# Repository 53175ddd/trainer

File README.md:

# trainer でできること

Arduino を使ったプログラミング学習用の教材です．段階を踏んで様々なことを学ぶことができるよう開発を進めています．

## 本リポジトリで管理されているもの

- 専用の開発ボード
  - `./boards/`
- 各種サンプルコード
  - `./samples/`
- 各種ドキュメント（Web ページとして公開）
  - `./docs/`
- 関連リンク

## ハードウェア

実習用に，秋月電子で購入できる RP2040 搭載のマイコンボード「AE-RP2040」を使用するハードウェア「trainer-pico」を用意しています．

基板イメージ：<https://kicanvas.org/?repo=https%3A%2F%2Fgithub.com%2F53175ddd%2Ftrainer%2Ftree%2Fmaster%2Fboards%2Ftrainer-pico>

// 基板が出来上がったら Booth の購入リンクを追加する

## ドキュメント

// ある程度開発が進んでから整備する  
// `./docs/` 以下に配置し GitHub Pages で公開の上，そのリンクをここに貼る

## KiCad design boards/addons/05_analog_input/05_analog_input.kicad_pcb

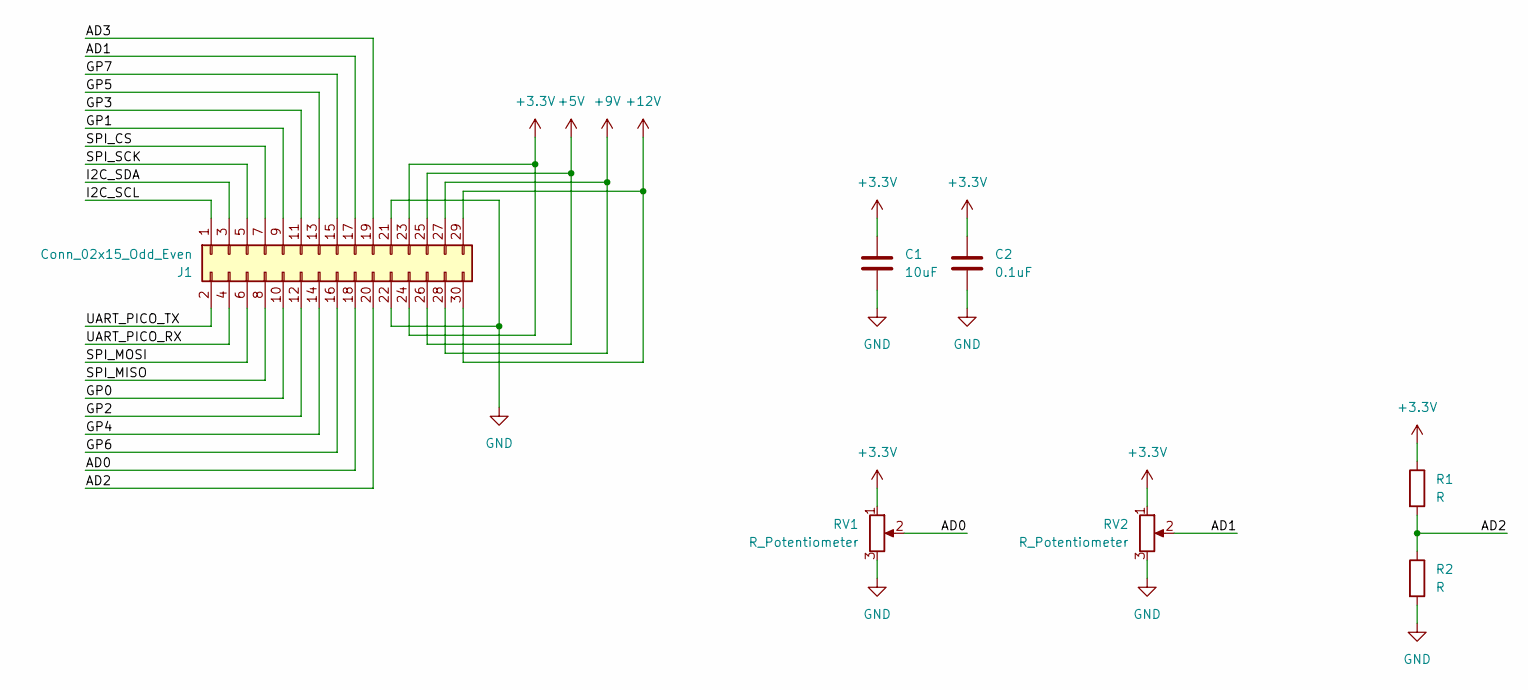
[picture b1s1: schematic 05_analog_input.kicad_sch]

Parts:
C1: 10uF; CP_Radial_D5.0mm_P2.00mm
C2: 0.1uF; C_Disc_D5.1mm_W3.2mm_P5.00mm
J1: Conn_02x15_Odd_Even; PinHeader_2x15_P2.54mm_Horizontal
R1: R; R_Radial_Power_L11.0mm_W7.0mm_P5.00mm
R2: R; R_Axial_DIN0207_L6.3mm_D2.5mm_P10.16mm_Horizontal
RV1, RV2: R_Potentiometer; Potentiometer_Bourns_PTA4543_Single_Slide

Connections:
+3.3V: C1.1, C2.1, J1.23, J1.24, R1.1, RV1.1, RV2.1
+5V: J1.25, J1.26
+9V: J1.27, J1.28
+12V: J1.29, J1.30
/AD0: J1.18, RV1.2
/AD1: J1.17, RV2.2
/AD2: J1.20, R1.2, R2.1
/AD3: J1.19
/GP0: J1.10
/GP1: J1.9
/GP2: J1.12
/GP3: J1.11
/GP4: J1.14
/GP5: J1.13
/GP6: J1.16
/GP7: J1.15
/I2C_SCL: J1.1
/I2C_SDA: J1.3
/SPI_CS: J1.7
/SPI_MISO: J1.8
/SPI_MOSI: J1.6
/SPI_SCK: J1.5
/UART_PICO_RX: J1.4
/UART_PICO_TX: J1.2
GND: C1.2, C2.2, J1.21, J1.22, R2.2, RV1.3, RV2.3

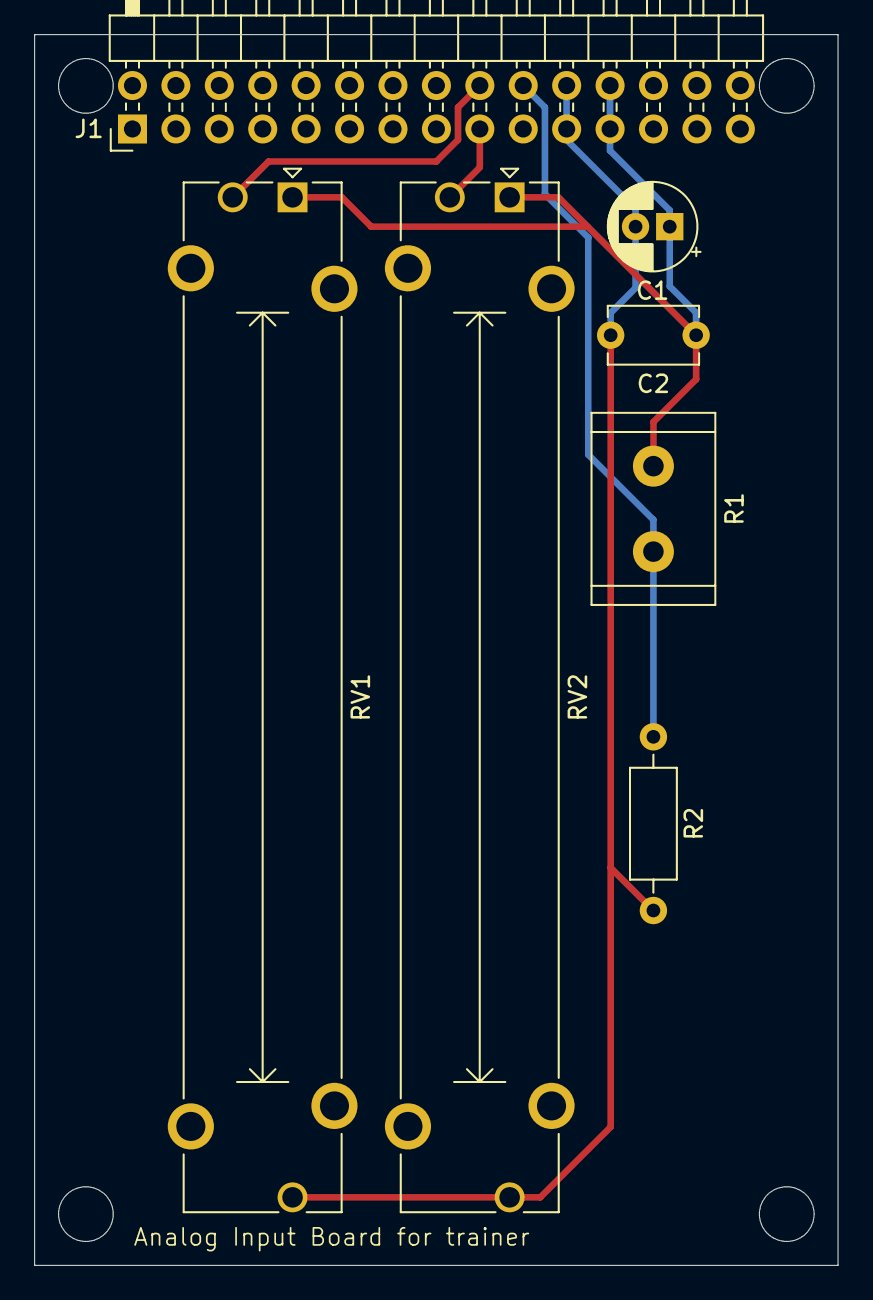
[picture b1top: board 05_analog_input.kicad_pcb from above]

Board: 2 copper layers, 47.0 x 72.0 mm, 7 parts (0 on the bottom side), 8 nets.

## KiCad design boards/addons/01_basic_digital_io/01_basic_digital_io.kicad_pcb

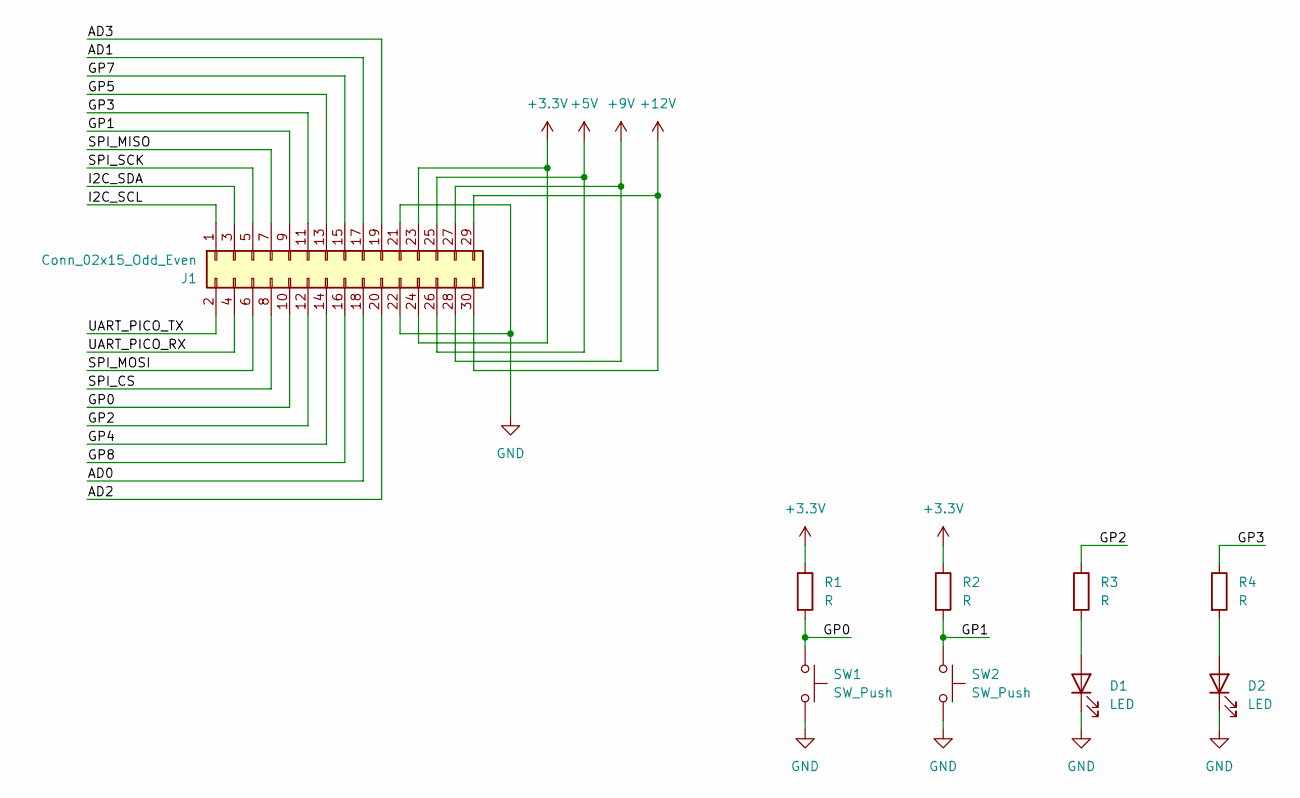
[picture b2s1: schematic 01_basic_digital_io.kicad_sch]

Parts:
D1, D2: LED; LED_D5.0mm
J1: Conn_02x15_Odd_Even; PinHeader_2x15_P2.54mm_Horizontal
R1, R2, R3, R4: R; R_Axial_DIN0207_L6.3mm_D2.5mm_P10.16mm_Horizontal
SW1, SW2: SW_Push; SW_PUSH-12mm

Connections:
+3.3V: J1.23, J1.24, R1.1, R2.1
+5V: J1.25, J1.26
+9V: J1.27, J1.28
+12V: J1.29, J1.30
/AD0: J1.18
/AD1: J1.17
/AD2: J1.20
/AD3: J1.19
/GP0: J1.10, R1.2, SW1.1
/GP1: J1.9, R2.2, SW2.1
/GP2: J1.12, R3.1
/GP3: J1.11, R4.1
/GP4: J1.14
/GP5: J1.13
/GP7: J1.15
/GP8: J1.16
/I2C_SCL: J1.1
/I2C_SDA: J1.3
/SPI_CS: J1.8
/SPI_SCK: J1.5
/UART_PICO_RX: J1.4
/UART_PICO_TX: J1.2
GND: D1.1 (K), D2.1 (K), J1.21, J1.22, SW1.2, SW2.2
unnamed: D1.2 (A), R3.2
unnamed: D2.2 (A), R4.2

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
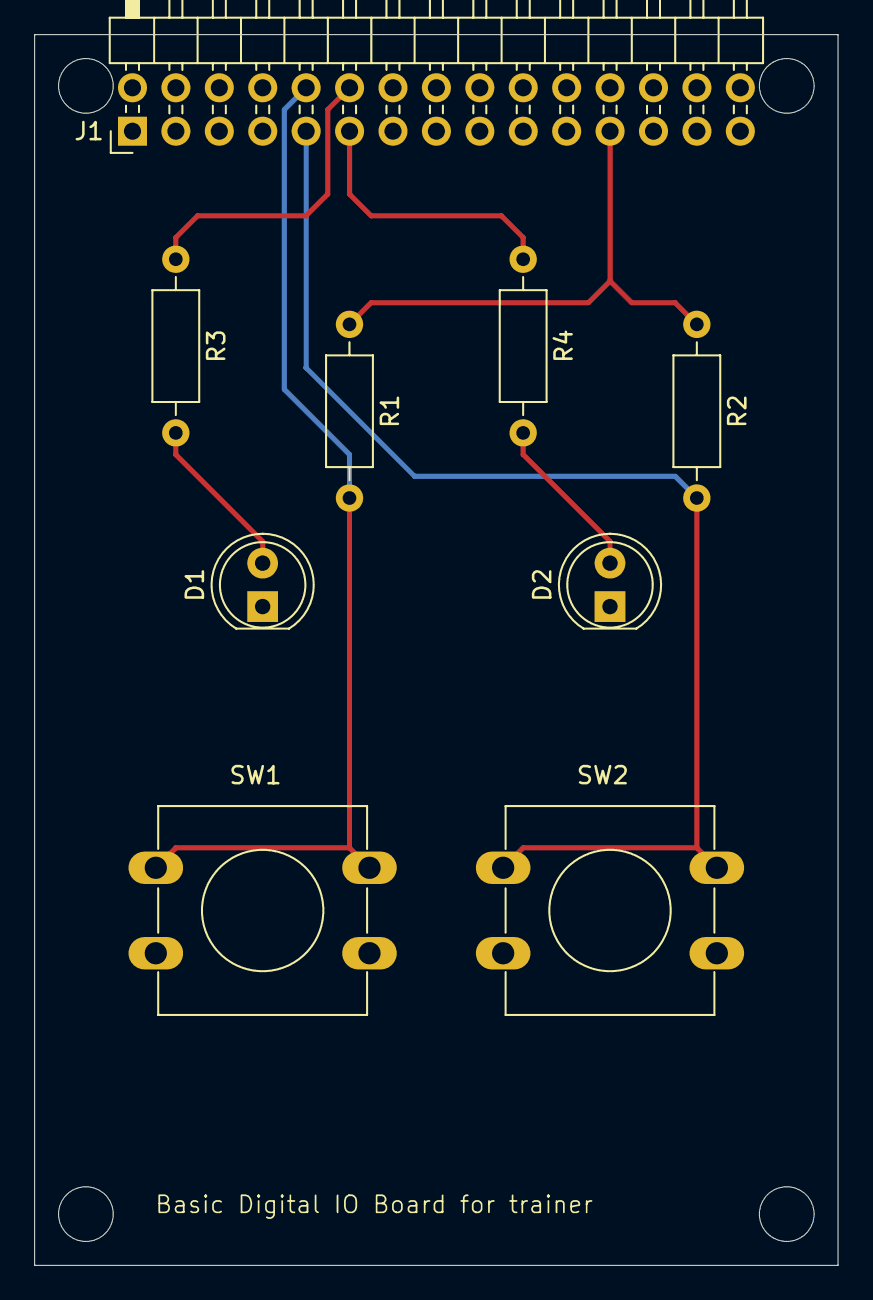
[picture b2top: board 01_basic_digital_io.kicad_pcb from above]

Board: 2 copper layers, 47.0 x 72.0 mm, 9 parts (0 on the bottom side), 12 nets.

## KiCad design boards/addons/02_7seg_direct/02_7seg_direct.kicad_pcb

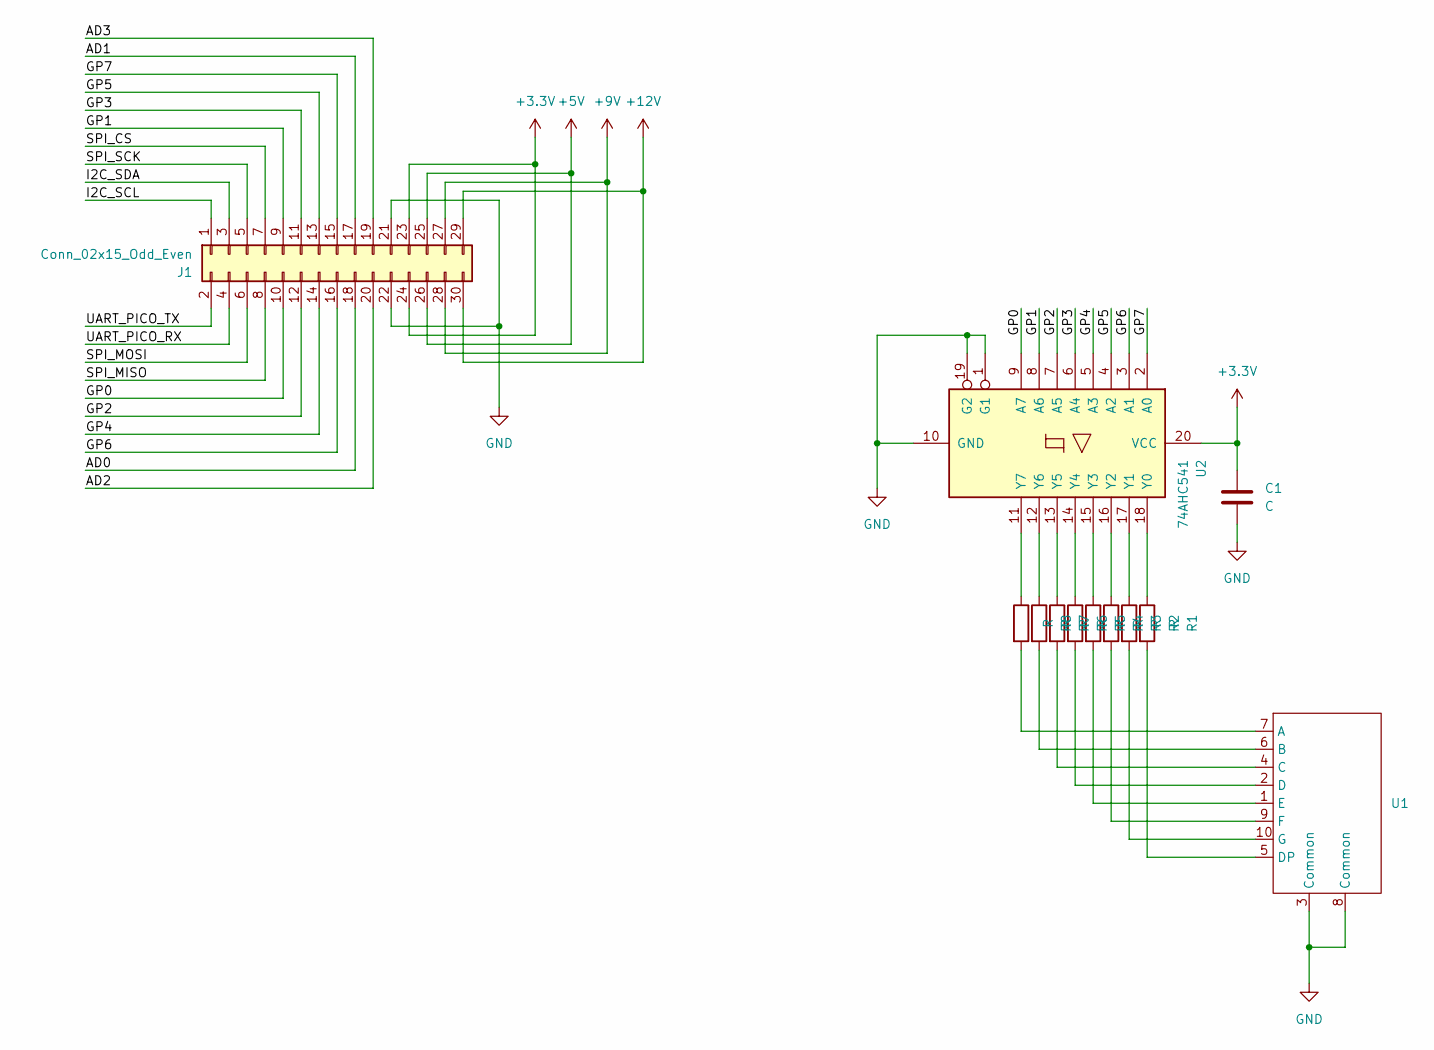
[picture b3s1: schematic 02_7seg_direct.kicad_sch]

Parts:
C1: C; C_Disc_D4.7mm_W2.5mm_P5.00mm
J1: Conn_02x15_Odd_Even; PinHeader_2x15_P2.54mm_Horizontal
R1, R2, R3, R4, R5, R6, R7, R8: R; R_Axial_DIN0207_L6.3mm_D2.5mm_P10.16mm_Horizontal
U1: OSL10561
U2: 74AHC541; DIP-20_W7.62mm_Socket

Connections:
+3.3V: C1.1, J1.23, J1.24, U2.20 (VCC)
+5V: J1.25, J1.26
+9V: J1.27, J1.28
+12V: J1.29, J1.30
/AD0: J1.18
/AD1: J1.17
/AD2: J1.20
/AD3: J1.19
/GP0: J1.10, U2.9 (A7)
/GP1: J1.9, U2.8 (A6)
/GP2: J1.12, U2.7 (A5)
/GP3: J1.11, U2.6 (A4)
/GP4: J1.14, U2.5 (A3)
/GP5: J1.13, U2.4 (A2)
/GP6: J1.16, U2.3 (A1)
/GP7: J1.15, U2.2 (A0)
/I2C_SCL: J1.1
/I2C_SDA: J1.3
/SPI_CS: J1.7
/SPI_MISO: J1.8
/SPI_MOSI: J1.6
/SPI_SCK: J1.5
/UART_PICO_RX: J1.4
/UART_PICO_TX: J1.2
GND: C1.2, J1.21, J1.22, U1.3 (Common), U1.8 (Common), U2.1 (G1), U2.10 (GND), U2.19 (G2)
unnamed: R8.2, U1.7 (A)
unnamed: R7.2, U1.6 (B)
unnamed: R6.2, U1.4 (C)
unnamed: R5.2, U1.2 (D)
unnamed: R1.2, U1.5 (DP)
unnamed: R4.2, U1.1 (E)
unnamed: R3.2, U1.9 (F)
unnamed: R2.2, U1.10 (G)
unnamed: R1.1, U2.18 (Y0)
unnamed: R2.1, U2.17 (Y1)
unnamed: R3.1, U2.16 (Y2)
unnamed: R4.1, U2.15 (Y3)
unnamed: R5.1, U2.14 (Y4)
unnamed: R6.1, U2.13 (Y5)
unnamed: R7.1, U2.12 (Y6)
unnamed: R8.1, U2.11 (Y7)

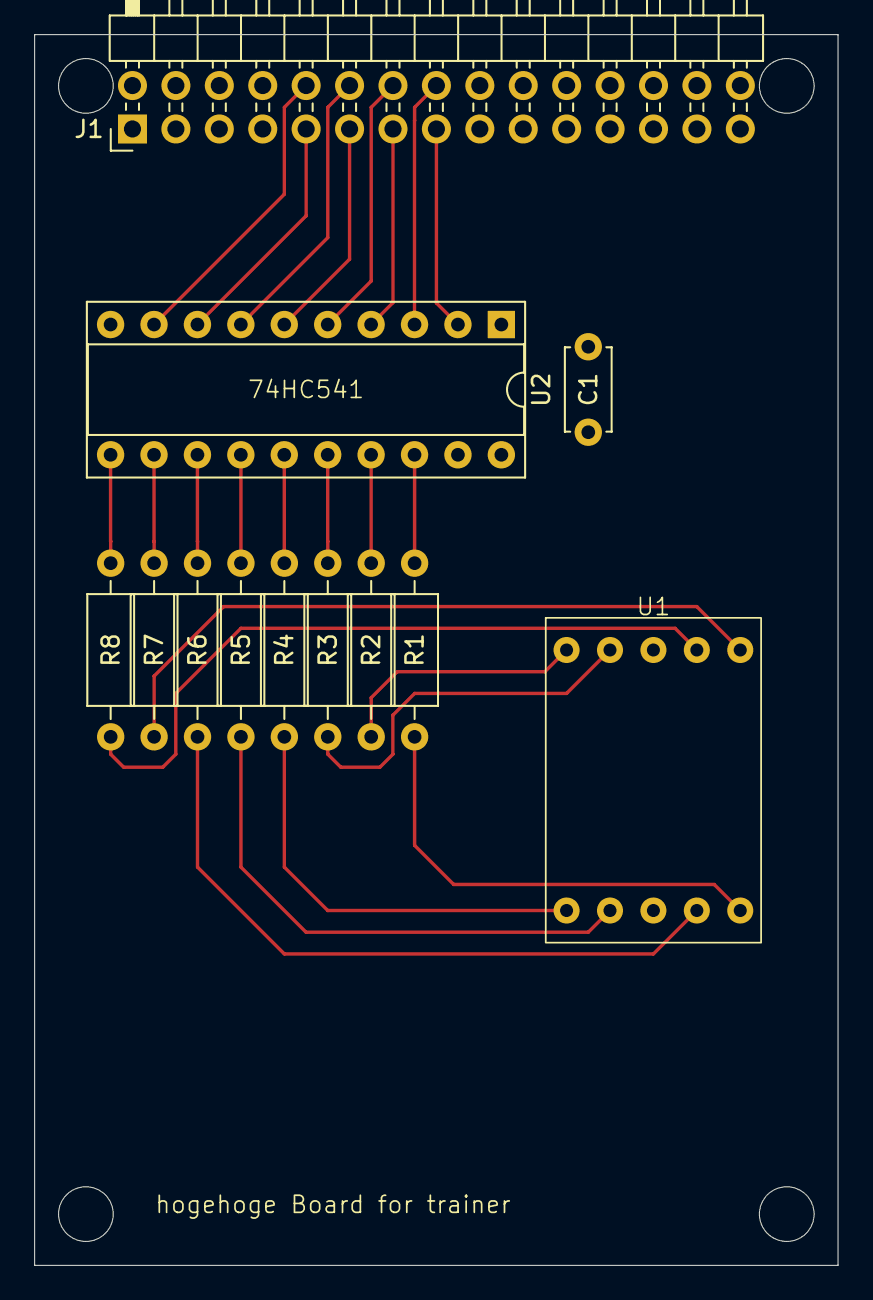
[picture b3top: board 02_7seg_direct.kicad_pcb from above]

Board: 2 copper layers, 47.0 x 72.0 mm, 12 parts (0 on the bottom side), 29 nets.

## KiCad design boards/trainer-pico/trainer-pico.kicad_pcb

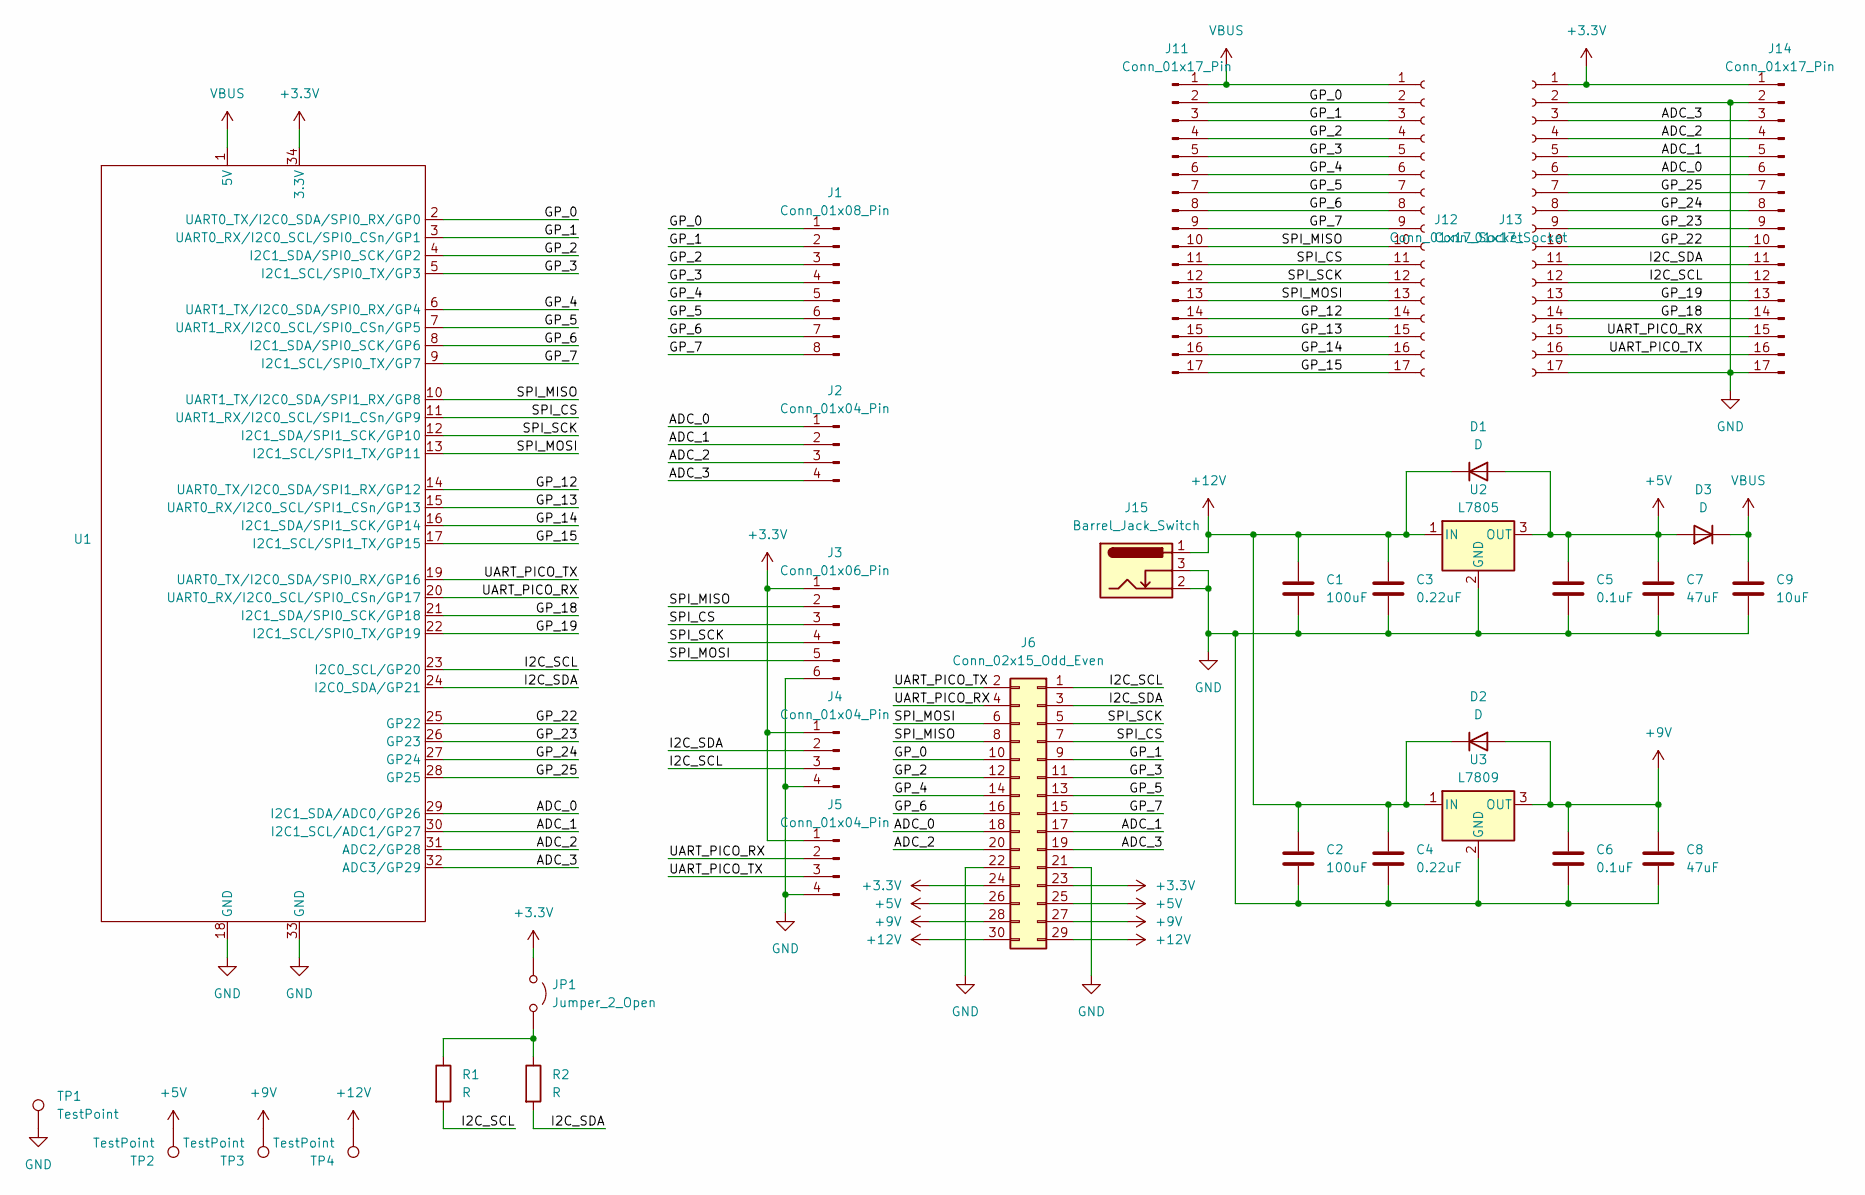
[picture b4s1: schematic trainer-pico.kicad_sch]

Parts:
C1, C2: 100uF; CP_Radial_D8.0mm_P3.50mm
C3, C4: 0.22uF; C_0805_2012Metric; LCSC C161262
C5, C6: 0.1uF; C_0603_1608Metric; LCSC C77055
C7, C8: 47uF; CP_Radial_D6.3mm_P2.50mm
C9: 10uF; C_1206_3216Metric; LCSC C77092
D1, D2, D3: D; D_SOD-123F; LCSC C83528
J1: Conn_01x08_Pin; PinHeader_1x08_P2.54mm_Vertical
J2, J4, J5: Conn_01x04_Pin; PinHeader_1x04_P2.54mm_Vertical
J3: Conn_01x06_Pin; PinHeader_1x06_P2.54mm_Vertical
J6: Conn_02x15_Odd_Even; PinSocket_2x15_P2.54mm_Horizontal
J11, J14: Conn_01x17_Pin; PinHeader_1x17_P2.54mm_Vertical
J12, J13: Conn_01x17_Socket; PinSocket_1x17_P2.54mm_Vertical
J15: Barrel_Jack_Switch; BarrelJack_Horizontal
JP1: Jumper_2_Open; SolderJumper-2_P1.3mm_Open_RoundedPad1.0x1.5mm
R1, R2: R; R_0603_1608Metric; LCSC C98220
TP1, TP2, TP3, TP4: TestPoint; PinHeader_1x01_P2.54mm_Vertical
U1: AE-RP2040
U2: L7805; TO-263-2; LCSC C86206
U3: L7809; TO-263-2; LCSC C262905

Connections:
+3.3V: J3.1, J4.1, J5.1, J6.23, J6.24, J13.1, J14.1, JP1.1 (A), U1.34 (3.3V)
+5V: C5.1, C7.1, D1.2 (A), D3.2 (A), J6.25, J6.26, TP2.1, U2.3 (OUT)
+9V: C6.1, C8.1, D2.2 (A), J6.27, J6.28, TP3.1, U3.3 (OUT)
+12V: C1.1, C2.1, C3.1, C4.1, D1.1 (K), D2.1 (K), J6.29, J6.30, J15.1, TP4.1, U2.1 (IN), U3.1 (IN)
/ADC_0: J2.1, J6.18, J13.6, J14.6, U1.29 (I2C1_SDA/ADC0/GP26)
/ADC_1: J2.2, J6.17, J13.5, J14.5, U1.30 (I2C1_SCL/ADC1/GP27)
/ADC_2: J2.3, J6.20, J13.4, J14.4, U1.31 (ADC2/GP28)
/ADC_3: J2.4, J6.19, J13.3, J14.3, U1.32 (ADC3/GP29)
/GP_0: J1.1, J6.10, J11.2, J12.2, U1.2 (UART0_TX/I2C0_SDA/SPI0_RX/GP0)
/GP_1: J1.2, J6.9, J11.3, J12.3, U1.3 (UART0_RX/I2C0_SCL/SPI0_CSn/GP1)
/GP_2: J1.3, J6.12, J11.4, J12.4, U1.4 (I2C1_SDA/SPI0_SCK/GP2)
/GP_3: J1.4, J6.11, J11.5, J12.5, U1.5 (I2C1_SCL/SPI0_TX/GP3)
/GP_4: J1.5, J6.14, J11.6, J12.6, U1.6 (UART1_TX/I2C0_SDA/SPI0_RX/GP4)
/GP_5: J1.6, J6.13, J11.7, J12.7, U1.7 (UART1_RX/I2C0_SCL/SPI0_CSn/GP5)
/GP_6: J1.7, J6.16, J11.8, J12.8, U1.8 (I2C1_SDA/SPI0_SCK/GP6)
/GP_7: J1.8, J6.15, J11.9, J12.9, U1.9 (I2C1_SCL/SPI0_TX/GP7)
/GP_12: J11.14, J12.14, U1.14 (UART0_TX/I2C0_SDA/SPI1_RX/GP12)
/GP_13: J11.15, J12.15, U1.15 (UART0_RX/I2C0_SCL/SPI1_CSn/GP13)
/GP_14: J11.16, J12.16, U1.16 (I2C1_SDA/SPI1_SCK/GP14)
/GP_15: J11.17, J12.17, U1.17 (I2C1_SCL/SPI1_TX/GP15)
/GP_18: J13.14, J14.14, U1.21 (I2C1_SDA/SPI0_SCK/GP18)
/GP_19: J13.13, J14.13, U1.22 (I2C1_SCL/SPI0_TX/GP19)
/GP_22: J13.10, J14.10, U1.25 (GP22)
/GP_23: J13.9, J14.9, U1.26 (GP23)
/GP_24: J13.8, J14.8, U1.27 (GP24)
/GP_25: J13.7, J14.7, U1.28 (GP25)
/I2C_SCL: J4.3, J6.1, J13.12, J14.12, R1.2, U1.23 (I2C0_SCL/GP20)
/I2C_SDA: J4.2, J6.3, J13.11, J14.11, R2.2, U1.24 (I2C0_SDA/GP21)
/SPI_CS: J3.3, J6.7, J11.11, J12.11, U1.11 (UART1_RX/I2C0_SCL/SPI1_CSn/GP9)
/SPI_MISO: J3.2, J6.8, J11.10, J12.10, U1.10 (UART1_TX/I2C0_SDA/SPI1_RX/GP8)
/SPI_MOSI: J3.5, J6.6, J11.13, J12.13, U1.13 (I2C1_SCL/SPI1_TX/GP11)
/SPI_SCK: J3.4, J6.5, J11.12, J12.12, U1.12 (I2C1_SDA/SPI1_SCK/GP10)
/UART_PICO_RX: J5.2, J6.4, J13.15, J14.15, U1.20 (UART0_RX/I2C0_SCL/SPI0_CSn/GP17)
/UART_PICO_TX: J5.3, J6.2, J13.16, J14.16, U1.19 (UART0_TX/I2C0_SDA/SPI0_RX/GP16)
GND: C1.2, C2.2, C3.2, C4.2, C5.2, C6.2, C7.2, C8.2, C9.2, J3.6, J4.4, J5.4, J6.21, J6.22, J13.2, J13.17, J14.2, J14.17, J15.2, J15.3, TP1.1, U1.18 (GND), U1.33 (GND), U2.2 (GND), U3.2 (GND)
unnamed: JP1.2 (B), R1.1, R2.1
VBUS: C9.1, D3.1 (K), J11.1, J12.1, U1.1 (5V)

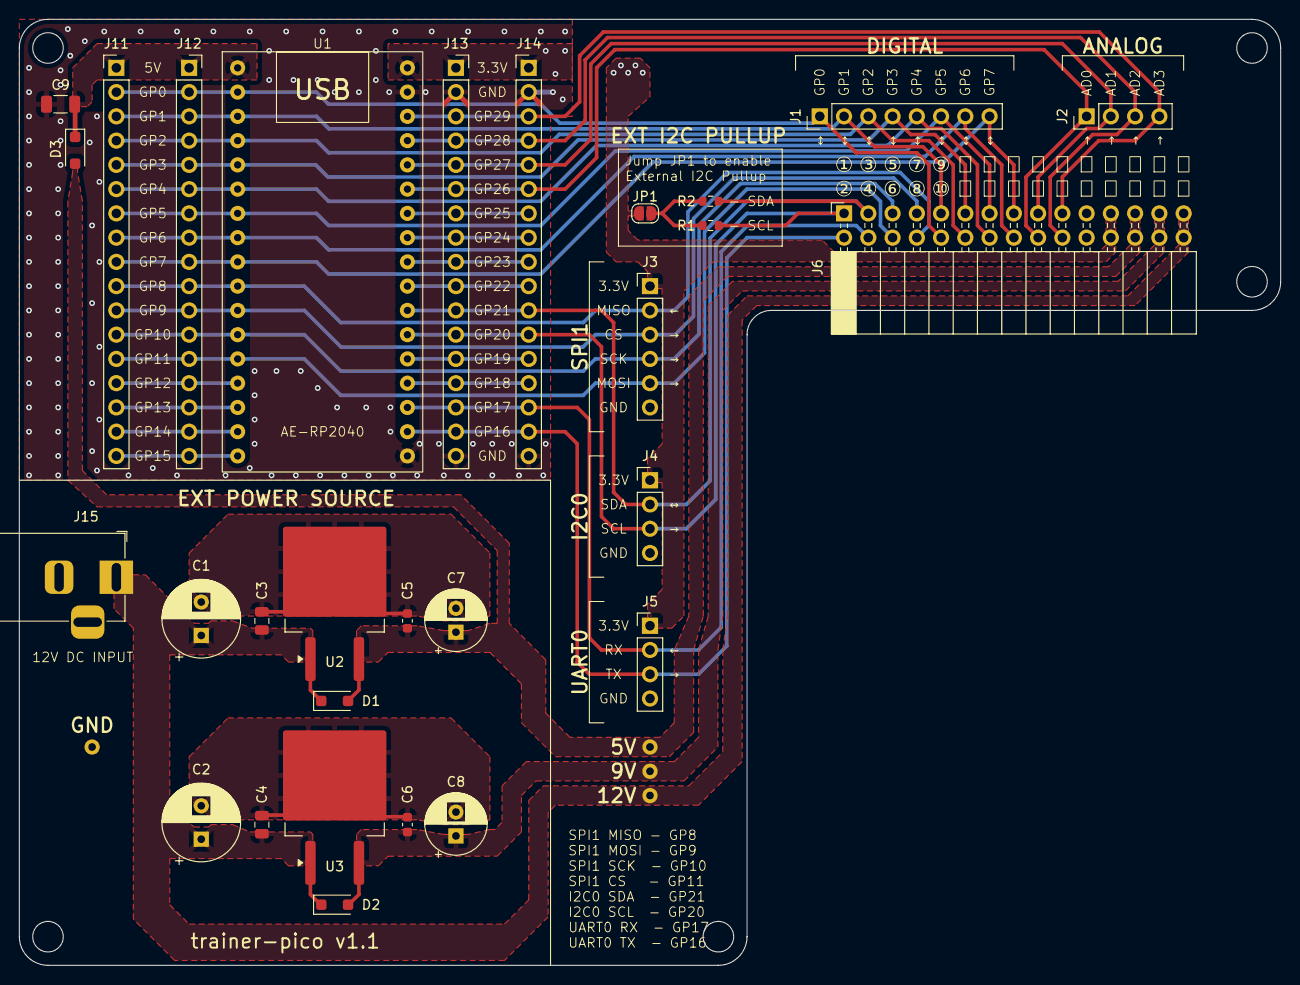
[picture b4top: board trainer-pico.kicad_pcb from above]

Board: 2 copper layers, 132.1 x 99.1 mm, 33 parts (0 on the bottom side), 37 nets.

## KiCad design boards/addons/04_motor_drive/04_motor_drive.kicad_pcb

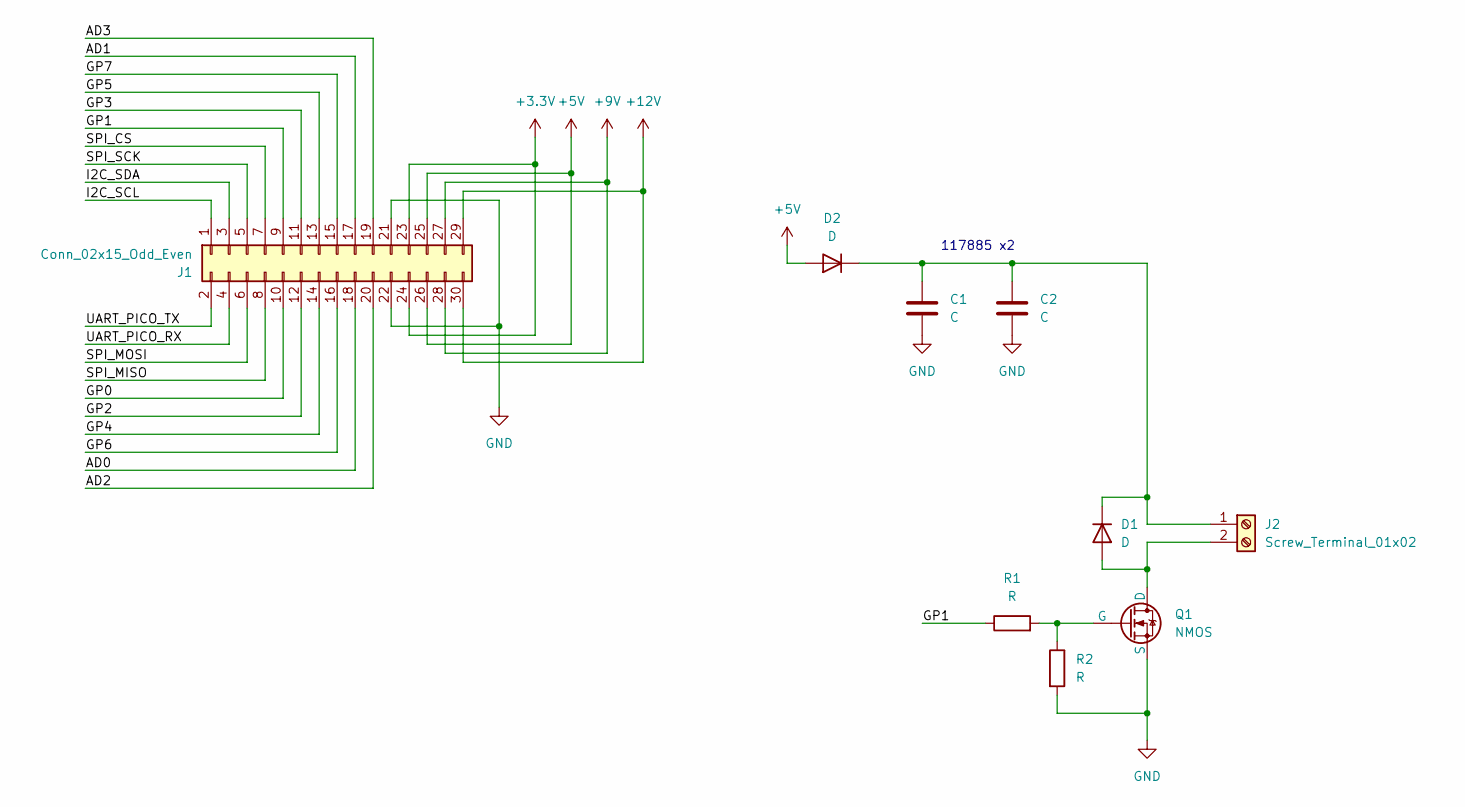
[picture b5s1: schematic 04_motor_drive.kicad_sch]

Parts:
C1, C2: C; CP_Radial_D10.0mm_P5.00mm
D1, D2: D; D_A-405_P10.16mm_Horizontal
J1: Conn_02x15_Odd_Even; PinHeader_2x15_P2.54mm_Horizontal
J2: Screw_Terminal_01x02; PinSocket_1x02_P2.54mm_Vertical
Q1: NMOS; TO-220-3_Vertical
R1, R2: R; R_Axial_DIN0207_L6.3mm_D2.5mm_P10.16mm_Horizontal

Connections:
+3.3V: J1.23, J1.24
+5V: D2.2 (A), J1.25, J1.26
+9V: J1.27, J1.28
+12V: J1.29, J1.30
/AD0: J1.18
/AD1: J1.17
/AD2: J1.20
/AD3: J1.19
/GP0: J1.10
/GP1: J1.9, R1.1
/GP2: J1.12
/GP3: J1.11
/GP4: J1.14
/GP5: J1.13
/GP6: J1.16
/GP7: J1.15
/I2C_SCL: J1.1
/I2C_SDA: J1.3
/SPI_CS: J1.7
/SPI_MISO: J1.8
/SPI_MOSI: J1.6
/SPI_SCK: J1.5
/UART_PICO_RX: J1.4
/UART_PICO_TX: J1.2
GND: C1.2, C2.2, J1.21, J1.22, Q1.3 (S), R2.2
unnamed: D1.2 (A), J2.2, Q1.1 (D)
unnamed: C1.1, C2.1, D1.1 (K), D2.1 (K), J2.1
unnamed: Q1.2 (G), R1.2, R2.1

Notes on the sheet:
117885 x2

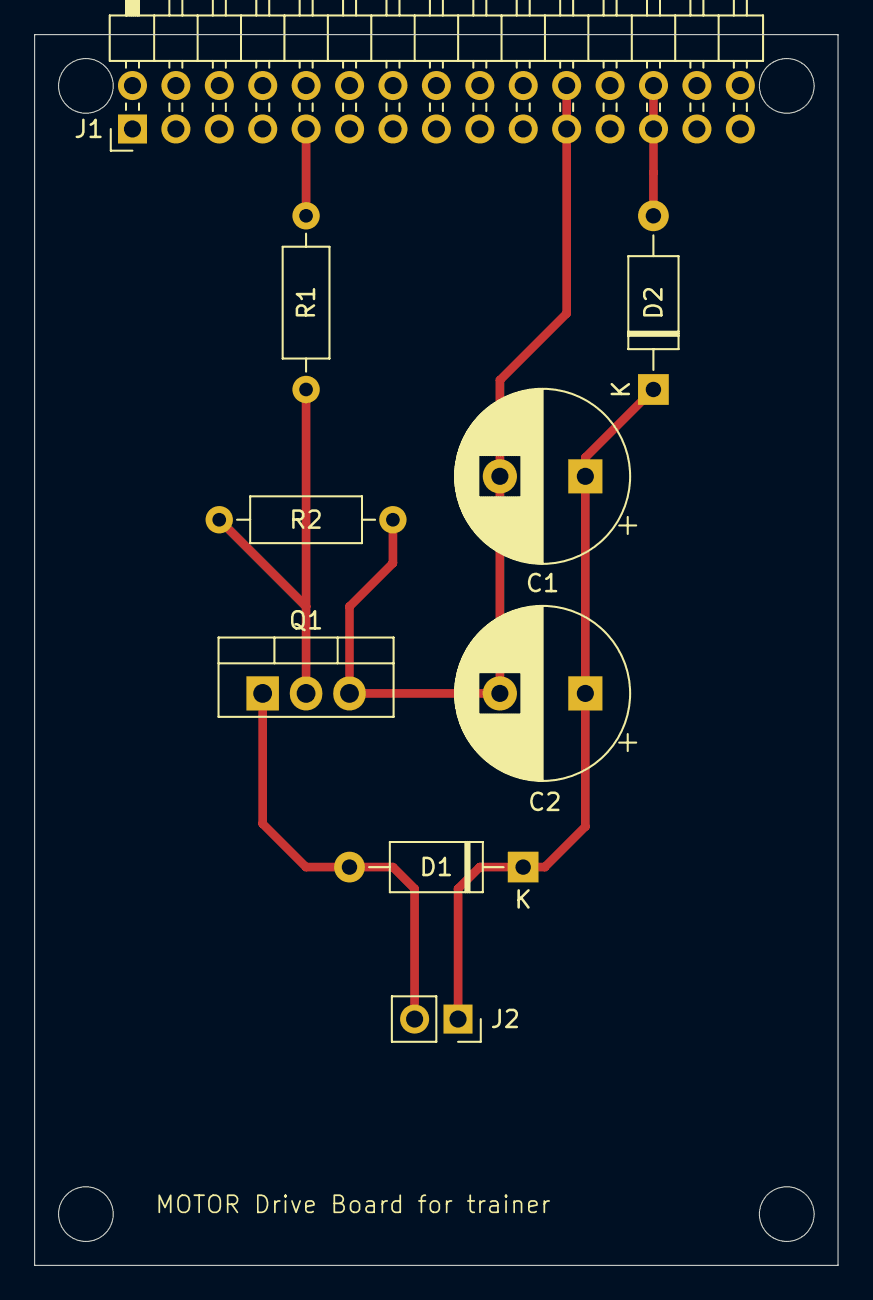
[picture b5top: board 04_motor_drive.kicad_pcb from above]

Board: 2 copper layers, 47.0 x 72.0 mm, 9 parts (0 on the bottom side), 9 nets.

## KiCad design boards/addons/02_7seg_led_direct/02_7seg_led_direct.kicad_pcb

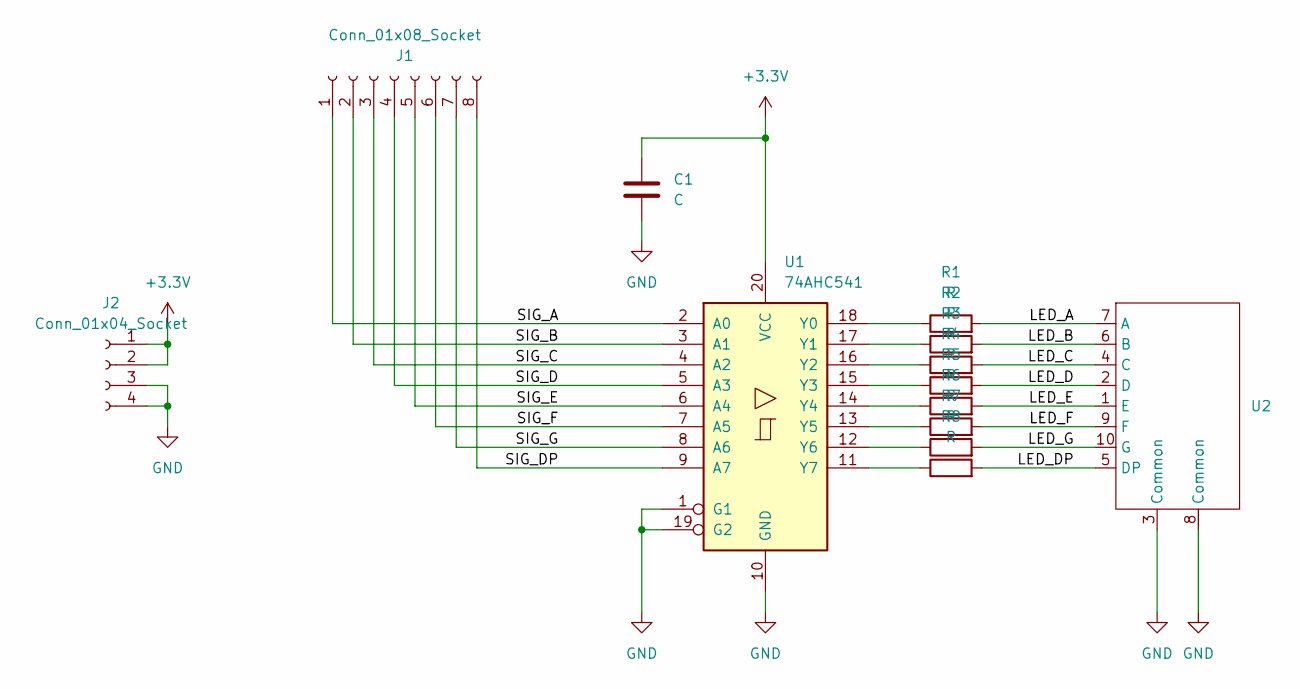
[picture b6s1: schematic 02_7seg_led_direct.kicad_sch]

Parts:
C1: C; C_Disc_D6.0mm_W2.5mm_P5.00mm
J1: Conn_01x08_Socket; PinSocket_1x08_P2.54mm_Vertical
J2: Conn_01x04_Socket; PinSocket_1x04_P2.54mm_Vertical
R1, R2, R3, R4, R5, R6, R7, R8: R; R_Axial_DIN0207_L6.3mm_D2.5mm_P10.16mm_Horizontal
U1: 74AHC541; DIP-20_W7.62mm
U2: OSL10561

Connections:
+3.3V: C1.1, J2.1, J2.2, U1.20 (VCC)
/LED_A: R1.2, U2.7 (A)
/LED_B: R2.2, U2.6 (B)
/LED_C: R3.2, U2.4 (C)
/LED_D: R4.2, U2.2 (D)
/LED_DP: R8.2, U2.5 (DP)
/LED_E: R5.2, U2.1 (E)
/LED_F: R6.2, U2.9 (F)
/LED_G: R7.2, U2.10 (G)
/SIG_A: J1.1, U1.2 (A0)
/SIG_B: J1.2, U1.3 (A1)
/SIG_C: J1.3, U1.4 (A2)
/SIG_D: J1.4, U1.5 (A3)
/SIG_DP: J1.8, U1.9 (A7)
/SIG_E: J1.5, U1.6 (A4)
/SIG_F: J1.6, U1.7 (A5)
/SIG_G: J1.7, U1.8 (A6)
GND: C1.2, J2.3, J2.4, U1.1 (G1), U1.10 (GND), U1.19 (G2), U2.3 (Common), U2.8 (Common)
unnamed: R1.1, U1.18 (Y0)
unnamed: R2.1, U1.17 (Y1)
unnamed: R3.1, U1.16 (Y2)
unnamed: R4.1, U1.15 (Y3)
unnamed: R5.1, U1.14 (Y4)
unnamed: R6.1, U1.13 (Y5)
unnamed: R7.1, U1.12 (Y6)
unnamed: R8.1, U1.11 (Y7)

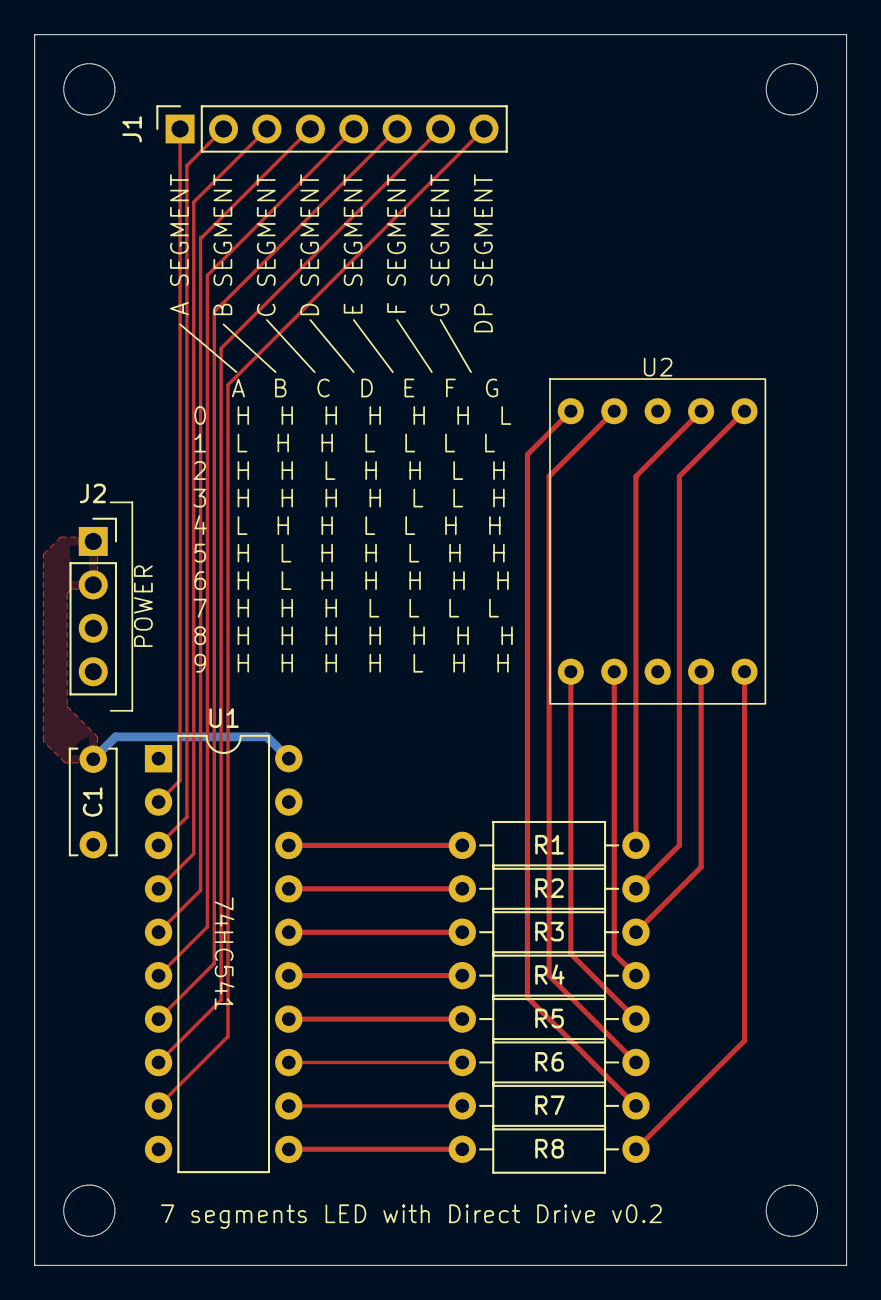
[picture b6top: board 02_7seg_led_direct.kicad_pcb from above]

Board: 2 copper layers, 47.5 x 72.0 mm, 13 parts (0 on the bottom side), 26 nets.

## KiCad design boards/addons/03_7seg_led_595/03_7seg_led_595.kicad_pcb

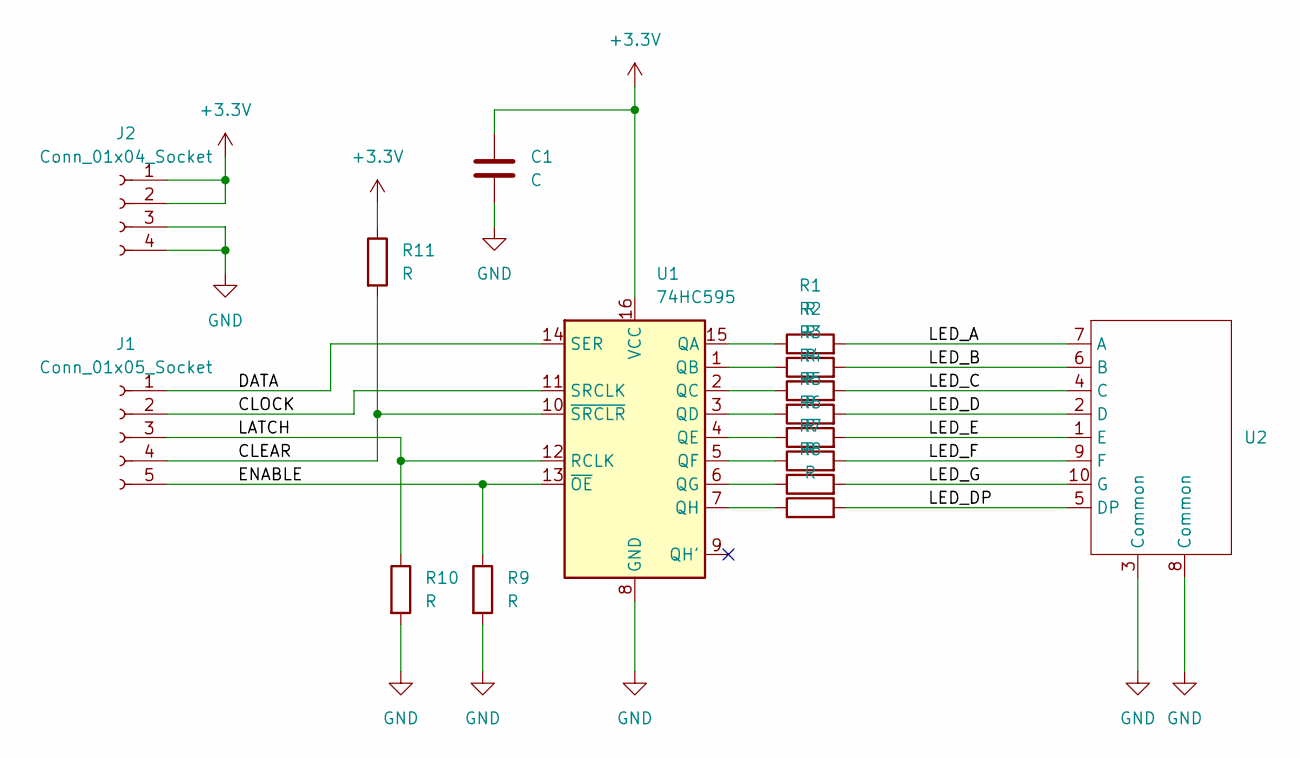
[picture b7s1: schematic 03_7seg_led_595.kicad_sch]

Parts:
C1: C; C_Disc_D6.0mm_W2.5mm_P5.00mm
J1: Conn_01x05_Socket; PinSocket_1x05_P2.54mm_Vertical
J2: Conn_01x04_Socket; PinSocket_1x04_P2.54mm_Vertical
R1, R2, R3, R4, R5, R6, R7, R8, R9, R10, R11: R; R_Axial_DIN0207_L6.3mm_D2.5mm_P10.16mm_Horizontal
U1: 74HC595; DIP-16_W7.62mm
U2: OSL10561

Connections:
+3.3V: C1.1, J2.1, J2.2, R11.1, U1.16 (VCC)
/CLEAR: J1.4, R11.2, U1.10 (~SRCLR)
/CLOCK: J1.2, U1.11 (SRCLK)
/DATA: J1.1, U1.14 (SER)
/ENABLE: J1.5, R9.1, U1.13 (~OE)
/LATCH: J1.3, R10.1, U1.12 (RCLK)
/LED_A: R1.2, U2.7 (A)
/LED_B: R2.2, U2.6 (B)
/LED_C: R3.2, U2.4 (C)
/LED_D: R4.2, U2.2 (D)
/LED_DP: R8.2, U2.5 (DP)
/LED_E: R5.2, U2.1 (E)
/LED_F: R6.2, U2.9 (F)
/LED_G: R7.2, U2.10 (G)
GND: C1.2, J2.3, J2.4, R9.2, R10.2, U1.8 (GND), U2.3 (Common), U2.8 (Common)
unnamed: R1.1, U1.15 (QA)
unnamed: R2.1, U1.1 (QB)
unnamed: R3.1, U1.2 (QC)
unnamed: R4.1, U1.3 (QD)
unnamed: R5.1, U1.4 (QE)
unnamed: R6.1, U1.5 (QF)
unnamed: R7.1, U1.6 (QG)
unnamed: R8.1, U1.7 (QH)
